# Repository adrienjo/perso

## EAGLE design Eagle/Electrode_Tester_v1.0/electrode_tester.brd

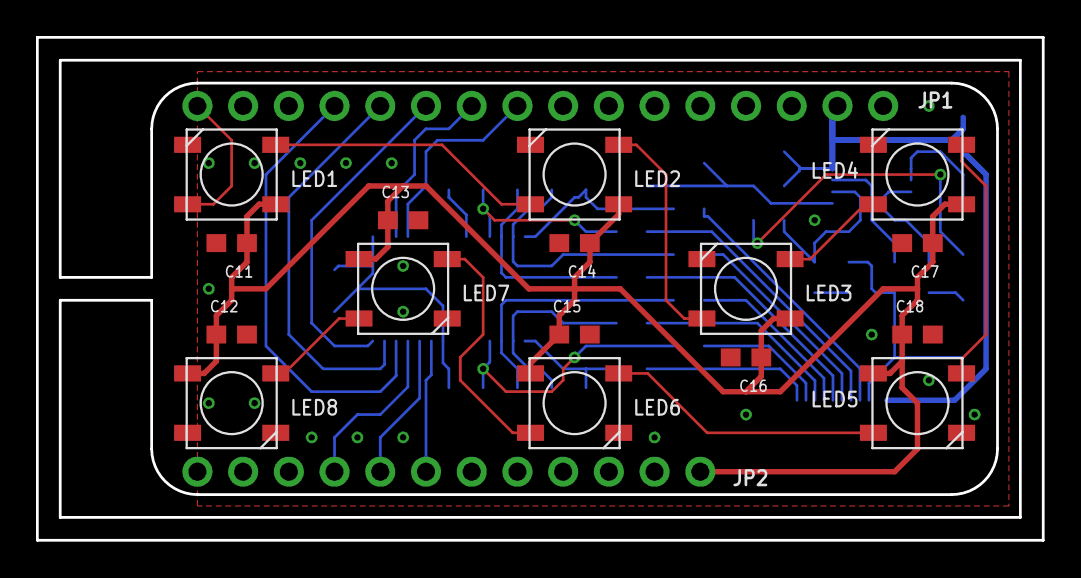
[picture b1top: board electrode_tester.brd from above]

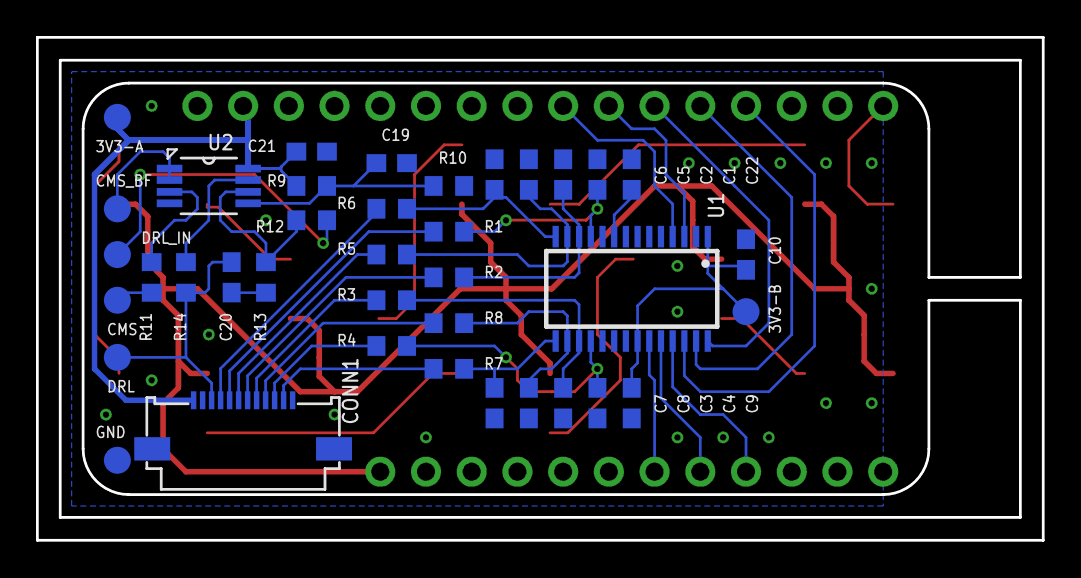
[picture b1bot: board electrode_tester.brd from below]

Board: 2 copper layers, 55.9 x 27.9 mm, 56 parts (38 on the bottom side), 45 nets.

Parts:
3V3-A, 3V3-B: TESTPAD_PROG; TP1.5MM
C1, C2, C3, C4, C5, C6, C7, C8, C9, C10, C11, C12, C13, C14, C15, C16, C17, C18, C19, C20, C21, C22: C0603
CMS: TESTPAD_PROG; TP1.5MM
CMS_BF: TESTPAD_PROG; TP1.5MM
CONN1: 505110-1292
DRL: TESTPAD_PROG; TP1.5MM
DRL_IN: TESTPAD_PROG; TP1.5MM
GND: TESTPAD_PROG; TP1.5MM
JP1: 1X16_ROUND
JP2: 1X12_ROUND
LED1, LED2, LED3, LED4, LED5, LED6, LED7, LED8: WS2812B5050; WS2812B
R1, R2, R3, R4, R5, R6, R7, R8, R9, R10, R11, R12, R13, R14: R0603
U1: ADS1248; TSSOP28
U2: LMP7702MM/NOPBVSSOP; VSSOP8

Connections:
3V3: 3V3-A.1, 3V3-B.1, C9.1, C10.1, C21.1, CONN1.12, JP1.15, R9.2, U1.1, U1.22, U2.8
ADC_/CS: JP2.8, U1.24
ADC_/DRDY: JP2.9, U1.25
ADC_/RST: JP1.8, U1.4
ADC_CLK: JP1.7, U1.3
ADC_START: JP2.7, U1.23
AIN0: C1.1, R1.2, U1.11
AIN1: C2.1, R2.2, U1.12
AIN2: C3.1, R3.2, U1.17
AIN3: C4.1, R4.2, U1.18
AIN4: C5.1, R5.2, U1.13
AIN5: C6.1, R6.2, U1.14
AIN6: C7.1, R7.2, U1.15
AIN7: C8.1, R8.2, U1.16
CMS: CMS.1, R11.2
CMS_BF: CMS_BF.1, U2.1, U2.2
DRL: C20.1, CONN1.10, DRL.1, R14.1
DRL_IN: DRL_IN.1, R12.1
E0: CONN1.8, R1.1
E1: CONN1.6, R2.1
E2: CONN1.5, R3.1
E3: CONN1.3, R4.1
E4: CONN1.7, R5.1
E5: CONN1.9, R6.1
E6: CONN1.2, R7.1
E7: CONN1.4, R8.1
GND: C1.2, C2.2, C3.2, C4.2, C5.2, C6.2, C7.2, C8.2, C9.2, C10.2, C11.2, C12.2, C13.2, C14.2, C15.2, C16.2, C17.2, C18.2, C19.2, C21.2, C22.2, CONN1.1, CONN1.MH1, CONN1.MH2, GND.1, JP1.13, LED1.3-GND, LED2.3-GND, LED3.3-GND, LED4.3-GND, LED5.3-GND, LED6.3-GND, LED7.3-GND, LED8.3-GND, R10.1, U1.2, U1.8, U1.10, U1.21, U2.4
LEDS_IN: JP1.1, LED1.4-DIN
unnamed: LED1.2-DOUT, LED2.4-DIN
unnamed: LED2.2-DOUT, LED3.4-DIN
unnamed: LED3.2-DOUT, LED4.4-DIN
unnamed: LED4.2-DOUT, LED5.4-DIN
unnamed: LED5.2-DOUT, LED6.4-DIN
unnamed: LED6.2-DOUT, LED7.4-DIN
unnamed: LED7.2-DOUT, LED8.4-DIN
unnamed: R11.1, U2.3
unnamed: C22.1, U1.9
unnamed: R12.2, R13.2, U2.6
unnamed: C20.2, R13.1
unnamed: R14.2, U2.7
unnamed: C19.1, R9.1, R10.2, U2.5
SPI_MISO: JP1.4, U1.26
SPI_MOSI: JP1.5, U1.27
SPI_SCLK: JP1.6, U1.28
VBAT: C11.1, C12.1, C13.1, C14.1, C15.1, C16.1, C17.1, C18.1, JP2.1, LED1.1-VDD, LED2.1-VDD, LED3.1-VDD, LED4.1-VDD, LED5.1-VDD, LED6.1-VDD, LED7.1-VDD, LED8.1-VDD

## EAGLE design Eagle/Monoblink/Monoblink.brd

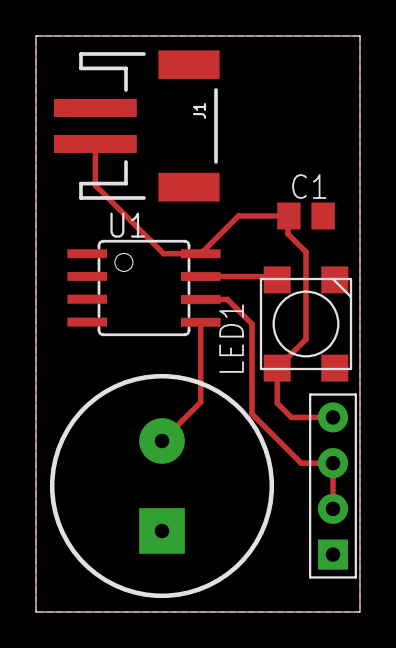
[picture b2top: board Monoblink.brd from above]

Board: 1 copper layer, 18.0 x 32.0 mm, 6 parts (0 on the bottom side), 5 nets.

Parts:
C1: C0805
J1: JST-2-SMD
LED1: NEOPIXEL; SMD5050
U1: ATTINY85; SOIC8
U$1: RF_CONN
U$2: PIEZO; PS1240P02BT

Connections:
GND: C1.2, J1.1, LED1.1, U1.4, U$1.1, U$2.V-
LED_DATA_IN: LED1.2, U1.7
PIEZO_IN: U1.5, U$2.V+
RF_DATA_OUT: U1.6, U$1.2, U$1.3
VCC: C1.1, J1.2, LED1.3, U1.8, U$1.4

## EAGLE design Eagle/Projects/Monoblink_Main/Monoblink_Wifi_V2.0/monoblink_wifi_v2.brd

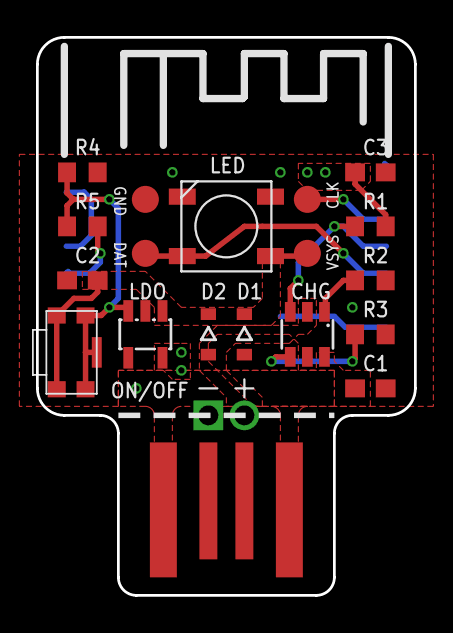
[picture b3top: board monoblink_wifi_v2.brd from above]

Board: 2 copper layers, 21.0 x 31.0 mm, 21 parts (1 on the bottom side), 13 nets.

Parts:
C1, C2: 0.1u; C0603
C3: C0603
CHG: BQ21040; SOT23-6
CLK: TESTPAD_PROG; TP1.5MM
D1, D2: NSR0320MW2T1G; SOD323
DAT: TESTPAD_PROG; TP1.5MM
GND: TESTPAD_PROG; TP1.5MM
LDO: TLV755P; SOT23-5
LED: WS2812B5050; WS2812B
LP402025: 150mAh; BATT_CON
ON/OFF: KMS231GPLFSNO_PEGS; KMS231GLFS
R1, R2, R5: 10K; R0603
R3: 6.8K; R0603
R4: 100K; R0603
U$2: USB_PCB; USB_PADS
VSYS: TESTPAD_PROG; TP1.5MM
WROOM-02: ESP-WROOM-02FRONT-FACE; FRONT-FACE

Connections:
/CHG: CHG.3, R1.2, WROOM-02.4
/SD: R5.1, WROOM-02.14
GND: C1.2, C2.2, C3.2, CHG.5, GND.1, LDO.2, LED.3-GND, LP402025.V-, R2.2, R3.2, R4.1, U$2.GND, WROOM-02.6, WROOM-02.9, WROOM-02.13, WROOM-02.18
IO16-RST: WROOM-02.15, WROOM-02.17
ISET: CHG.4, R3.1
LDO_EN: LDO.3, ON/OFF.2, ON/OFF.3, ON/OFF.4, R4.2, R5.2
LED_CLK: CLK.1, WROOM-02.3
LED_DATA: DAT.1, LED.4-DIN, WROOM-02.5
TS: CHG.1, R2.1
VBAT: CHG.2, D2.2, LP402025.V+
VCC_2V8: C3.1, LDO.5, R1.1, WROOM-02.1, WROOM-02.2, WROOM-02.7
VSYS: C2.1, D1.1, D2.1, LDO.1, LED.1-VDD, ON/OFF.1, ON/OFF.5, VSYS.1
VUSB_5V: C1.1, CHG.6, D1.2, U$2.V_SUPPLY

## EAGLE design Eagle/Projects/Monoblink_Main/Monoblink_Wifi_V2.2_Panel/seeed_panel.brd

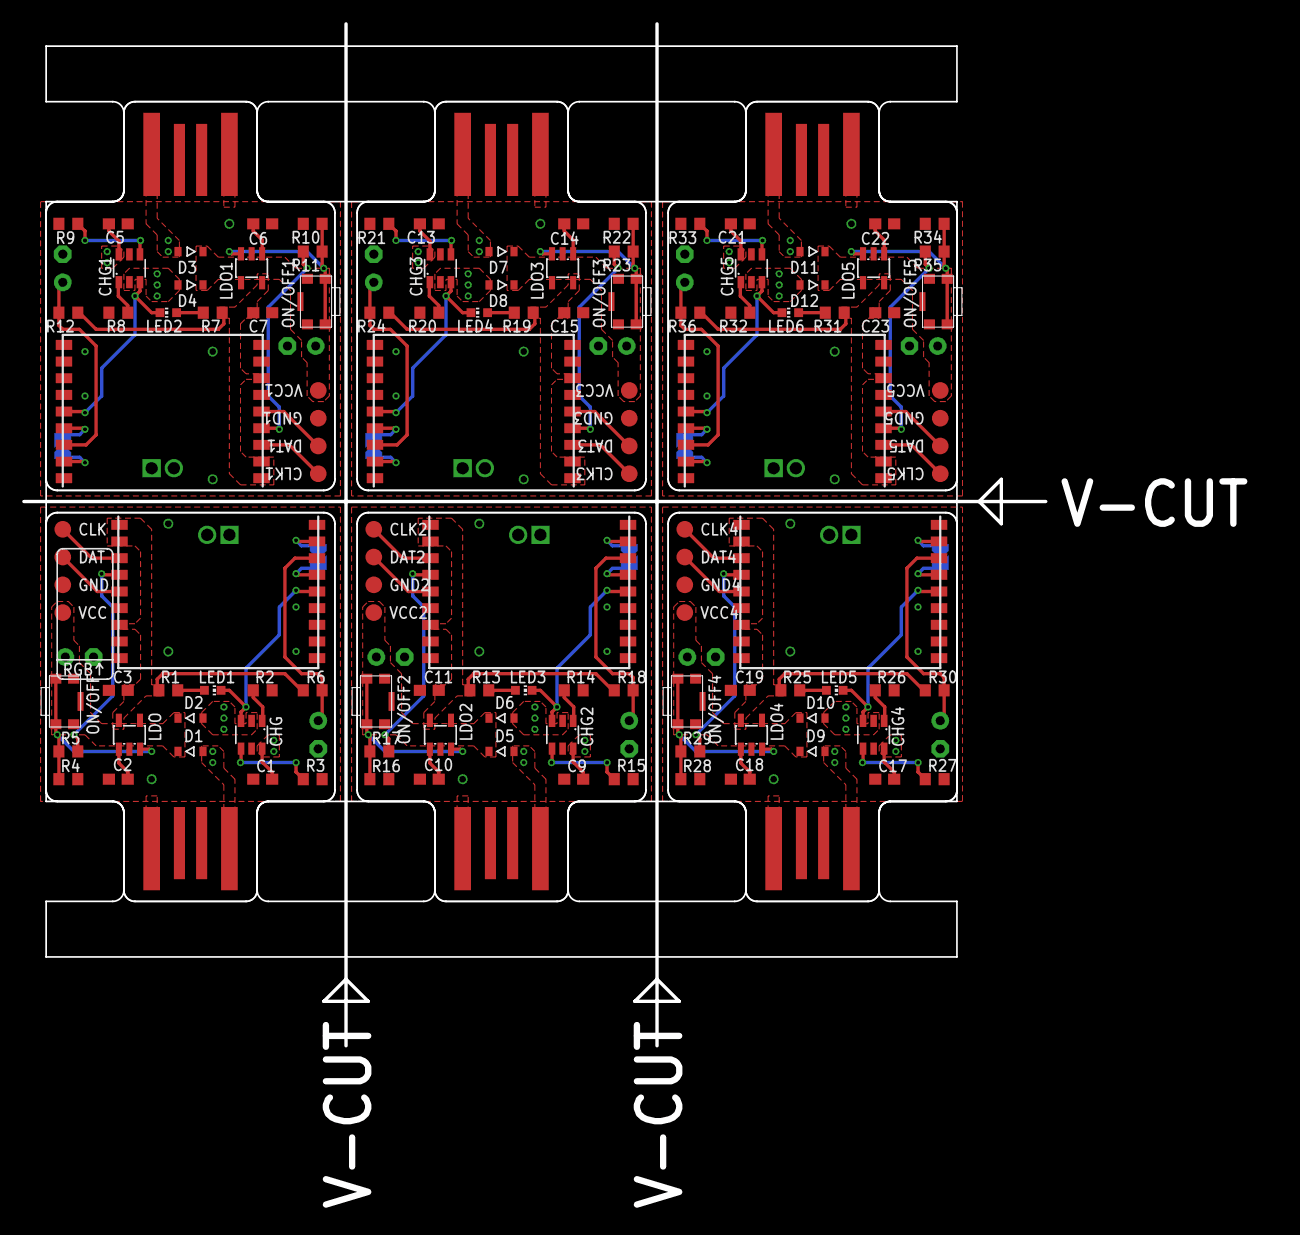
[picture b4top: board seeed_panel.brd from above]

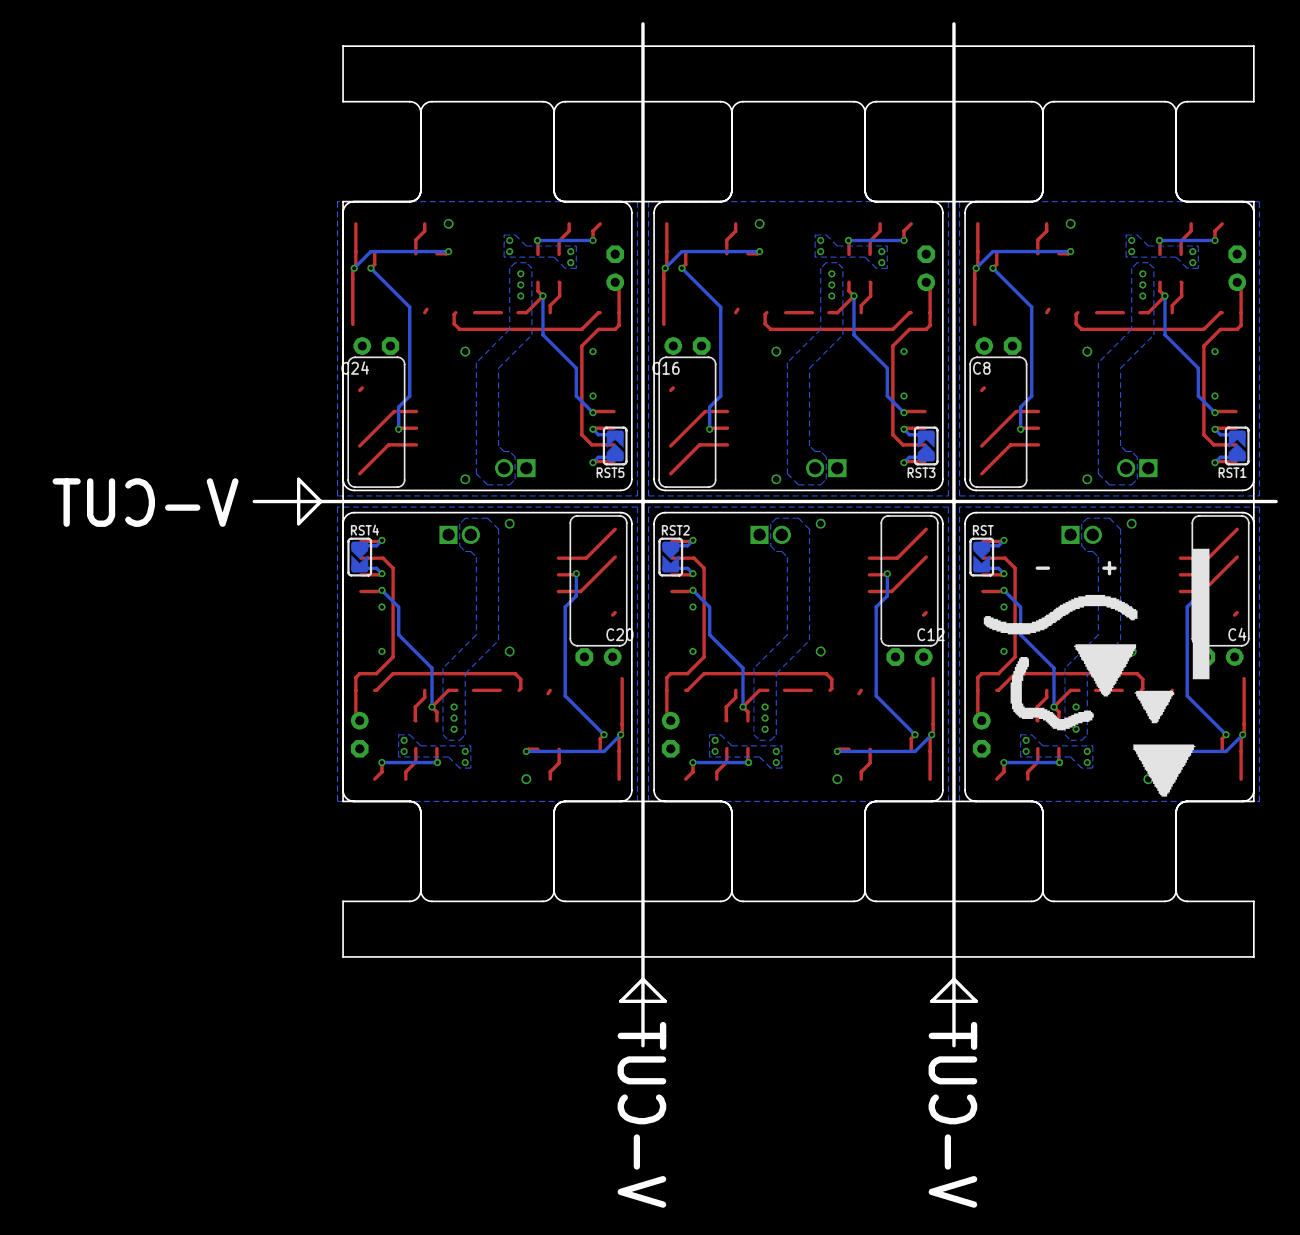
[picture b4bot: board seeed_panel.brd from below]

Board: 2 copper layers, 82.0 x 82.0 mm, 150 parts (12 on the bottom side), 96 nets.

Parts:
C1, C2, C5, C6, C9, C10, C13, C14, C17, C18, C21, C22: 0.1u; C0603
C3, C7, C11, C15, C19, C23: C0603
C4, C8, C12, C16, C20, C24: CAP_5MM_L; TT2D5L
CHG, CHG1, CHG2, CHG3, CHG4, CHG5: BQ21040; SOT23-6
CLK, CLK1, CLK2, CLK3, CLK4, CLK5: TESTPAD_PROG; TP1.5MM
D1, D2, D3, D4, D5, D6, D7, D8, D9, D10, D11, D12: NSR0320MW2T1G; SOD323
DAT, DAT1, DAT2, DAT3, DAT4, DAT5: TESTPAD_PROG; TP1.5MM
GND, GND1, GND2, GND3, GND4, GND5: TESTPAD_PROG; TP1.5MM
LDO, LDO1, LDO2, LDO3, LDO4, LDO5: TLV755P; SOT23-5
LED1, LED2, LED3, LED4, LED5, LED6: CHIP-LED0603
LP1, LP2, LP3, LP4, LP5, LP402025: 150mAh; BATT_CON
ON/OFF, ON/OFF1, ON/OFF2, ON/OFF3, ON/OFF4, ON/OFF5: KMS231GPLFSNO_PEGS; KMS231GLFS
R1, R7, R13, R19, R25, R31: 220; R0603
R2, R5, R6, R8, R11, R12, R14, R17, R18, R20, R23, R24, R26, R29, R30, R32, R35, R36: 10K; R0603
R3, R9, R15, R21, R27, R33: 6.8K; R0603
R4, R10, R16, R22, R28, R34: 100K; R0603
RST, RST1, RST2, RST3, RST4, RST5: SOLDERJUMPER_ARROW_NOPASTE
U$1, U$4, U$6, U$8, U$10, U$12: 2PIN_STD
U$2, U$3, U$5, U$7, U$9, U$11: USB_PCB; USB_PADS
VCC, VCC1, VCC2, VCC3, VCC4, VCC5: TESTPAD_PROG; TP1.5MM
WROOM-01, WROOM-02, WROOM-03, WROOM-04, WROOM-05, WROOM-06: ESP-WROOM-02FRONT-FACE; FRONT-FACE

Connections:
/CHG-/LED: CHG.3, LED1.C, WROOM-02.14
/CHG-/LED1: CHG1.3, LED2.C, WROOM-01.14
/CHG-/LED2: CHG2.3, LED3.C, WROOM-03.14
/CHG-/LED3: CHG3.3, LED4.C, WROOM-04.14
/CHG-/LED4: CHG4.3, LED5.C, WROOM-05.14
/CHG-/LED5: CHG5.3, LED6.C, WROOM-06.14
/SD: R5.1, WROOM-02.4
/SD1: R11.1, WROOM-01.4
/SD2: R17.1, WROOM-03.4
/SD3: R23.1, WROOM-04.4
/SD4: R29.1, WROOM-05.4
/SD5: R35.1, WROOM-06.4
A0: R6.1, U$1.+, WROOM-02.16
A1: R12.1, U$4.+, WROOM-01.16
A2: R18.1, U$6.+, WROOM-03.16
A3: R24.1, U$8.+, WROOM-04.16
A4: R30.1, U$10.+, WROOM-05.16
A5: R36.1, U$12.+, WROOM-06.16
GND: C1.2, C2.2, C3.2, C4.-, CHG.5, GND.1, LDO.2, LP402025.V-, R2.2, R3.2, R4.1, U$1.-, U$2.GND, WROOM-02.6, WROOM-02.9, WROOM-02.13, WROOM-02.18
GND1: C5.2, C6.2, C7.2, C8.-, CHG1.5, GND1.1, LDO1.2, LP1.V-, R8.2, R9.2, R10.1, U$3.GND, U$4.-, WROOM-01.6, WROOM-01.9, WROOM-01.13, WROOM-01.18
GND2: C9.2, C10.2, C11.2, C12.-, CHG2.5, GND2.1, LDO2.2, LP2.V-, R14.2, R15.2, R16.1, U$5.GND, U$6.-, WROOM-03.6, WROOM-03.9, WROOM-03.13, WROOM-03.18
GND3: C13.2, C14.2, C15.2, C16.-, CHG3.5, GND3.1, LDO3.2, LP3.V-, R20.2, R21.2, R22.1, U$7.GND, U$8.-, WROOM-04.6, WROOM-04.9, WROOM-04.13, WROOM-04.18
GND4: C17.2, C18.2, C19.2, C20.-, CHG4.5, GND4.1, LDO4.2, LP4.V-, R26.2, R27.2, R28.1, U$9.GND, U$10.-, WROOM-05.6, WROOM-05.9, WROOM-05.13, WROOM-05.18
GND5: C21.2, C22.2, C23.2, C24.-, CHG5.5, GND5.1, LDO5.2, LP5.V-, R32.2, R33.2, R34.1, U$11.GND, U$12.-, WROOM-06.6, WROOM-06.9, WROOM-06.13, WROOM-06.18
IO3: RST1.1, WROOM-01.17
IO7: RST2.1, WROOM-03.17
IO10: RST3.1, WROOM-04.17
IO13: RST4.1, WROOM-05.17
IO16: RST.1, WROOM-02.17
IO17: RST5.1, WROOM-06.17
ISET: CHG.4, R3.1
ISET1: CHG1.4, R9.1
ISET2: CHG2.4, R15.1
ISET3: CHG3.4, R21.1
ISET4: CHG4.4, R27.1
ISET5: CHG5.4, R33.1
LDO_EN: LDO.3, ON/OFF.1, ON/OFF.5, R4.2, R5.2
LDO_EN1: LDO1.3, ON/OFF1.1, ON/OFF1.5, R10.2, R11.2
LDO_EN2: LDO2.3, ON/OFF2.1, ON/OFF2.5, R16.2, R17.2
LDO_EN3: LDO3.3, ON/OFF3.1, ON/OFF3.5, R22.2, R23.2
LDO_EN4: LDO4.3, ON/OFF4.1, ON/OFF4.5, R28.2, R29.2
LDO_EN5: LDO5.3, ON/OFF5.1, ON/OFF5.5, R34.2, R35.2
LED_CLK: CLK.1, WROOM-02.3
LED_CLK1: CLK1.1, WROOM-01.3
LED_CLK2: CLK2.1, WROOM-03.3
LED_CLK3: CLK3.1, WROOM-04.3
LED_CLK4: CLK4.1, WROOM-05.3
LED_CLK5: CLK5.1, WROOM-06.3
LED_DATA: DAT.1, WROOM-02.5
LED_DATA1: DAT1.1, WROOM-01.5
LED_DATA2: DAT2.1, WROOM-03.5
LED_DATA3: DAT3.1, WROOM-04.5
LED_DATA4: DAT4.1, WROOM-05.5
LED_DATA5: DAT5.1, WROOM-06.5
unnamed: LED1.A, R1.2
unnamed: LED2.A, R7.2
unnamed: LED3.A, R13.2
unnamed: LED4.A, R19.2
unnamed: LED5.A, R25.2
unnamed: LED6.A, R31.2
RST: RST.2, WROOM-02.15
RST1: RST1.2, WROOM-01.15
RST2: RST2.2, WROOM-03.15
RST3: RST3.2, WROOM-04.15
RST4: RST4.2, WROOM-05.15
RST5: RST5.2, WROOM-06.15
TS: CHG.1, R2.1
TS1: CHG1.1, R8.1
TS2: CHG2.1, R14.1
TS3: CHG3.1, R20.1
TS4: CHG4.1, R26.1
TS5: CHG5.1, R32.1
VBAT: CHG.2, D2.2, LP402025.V+
VBAT1: CHG1.2, D4.2, LP1.V+
VBAT2: CHG2.2, D6.2, LP2.V+
VBAT3: CHG3.2, D8.2, LP3.V+
VBAT4: CHG4.2, D10.2, LP4.V+
VBAT5: CHG5.2, D12.2, LP5.V+
VCC: C2.1, C4.+, D1.1, D2.1, LDO.1, ON/OFF.2, ON/OFF.3, ON/OFF.4, VCC.1
VCC1: C6.1, C8.+, D3.1, D4.1, LDO1.1, ON/OFF1.2, ON/OFF1.3, ON/OFF1.4, VCC1.1
VCC2: C10.1, C12.+, D5.1, D6.1, LDO2.1, ON/OFF2.2, ON/OFF2.3, ON/OFF2.4, VCC2.1
VCC3: C14.1, C16.+, D7.1, D8.1, LDO3.1, ON/OFF3.2, ON/OFF3.3, ON/OFF3.4, VCC3.1
VCC4: C18.1, C20.+, D9.1, D10.1, LDO4.1, ON/OFF4.2, ON/OFF4.3, ON/OFF4.4, VCC4.1
VCC5: C22.1, C24.+, D11.1, D12.1, LDO5.1, ON/OFF5.2, ON/OFF5.3, ON/OFF5.4, VCC5.1
VDD: C3.1, LDO.5, R1.1, R6.2, WROOM-02.1, WROOM-02.2, WROOM-02.7
VDD1: C7.1, LDO1.5, R7.1, R12.2, WROOM-01.1, WROOM-01.2, WROOM-01.7
VDD2: C11.1, LDO2.5, R13.1, R18.2, WROOM-03.1, WROOM-03.2, WROOM-03.7
VDD3: C15.1, LDO3.5, R19.1, R24.2, WROOM-04.1, WROOM-04.2, WROOM-04.7
VDD4: C19.1, LDO4.5, R25.1, R30.2, WROOM-05.1, WROOM-05.2, WROOM-05.7
VDD5: C23.1, LDO5.5, R31.1, R36.2, WROOM-06.1, WROOM-06.2, WROOM-06.7
VUSB_5V: C1.1, CHG.6, D1.2, U$2.V_SUPPLY
VUSB_5V1: C5.1, CHG1.6, D3.2, U$3.V_SUPPLY
VUSB_5V2: C9.1, CHG2.6, D5.2, U$5.V_SUPPLY
VUSB_5V3: C13.1, CHG3.6, D7.2, U$7.V_SUPPLY
VUSB_5V4: C17.1, CHG4.6, D9.2, U$9.V_SUPPLY
VUSB_5V5: C21.1, CHG5.6, D11.2, U$11.V_SUPPLY

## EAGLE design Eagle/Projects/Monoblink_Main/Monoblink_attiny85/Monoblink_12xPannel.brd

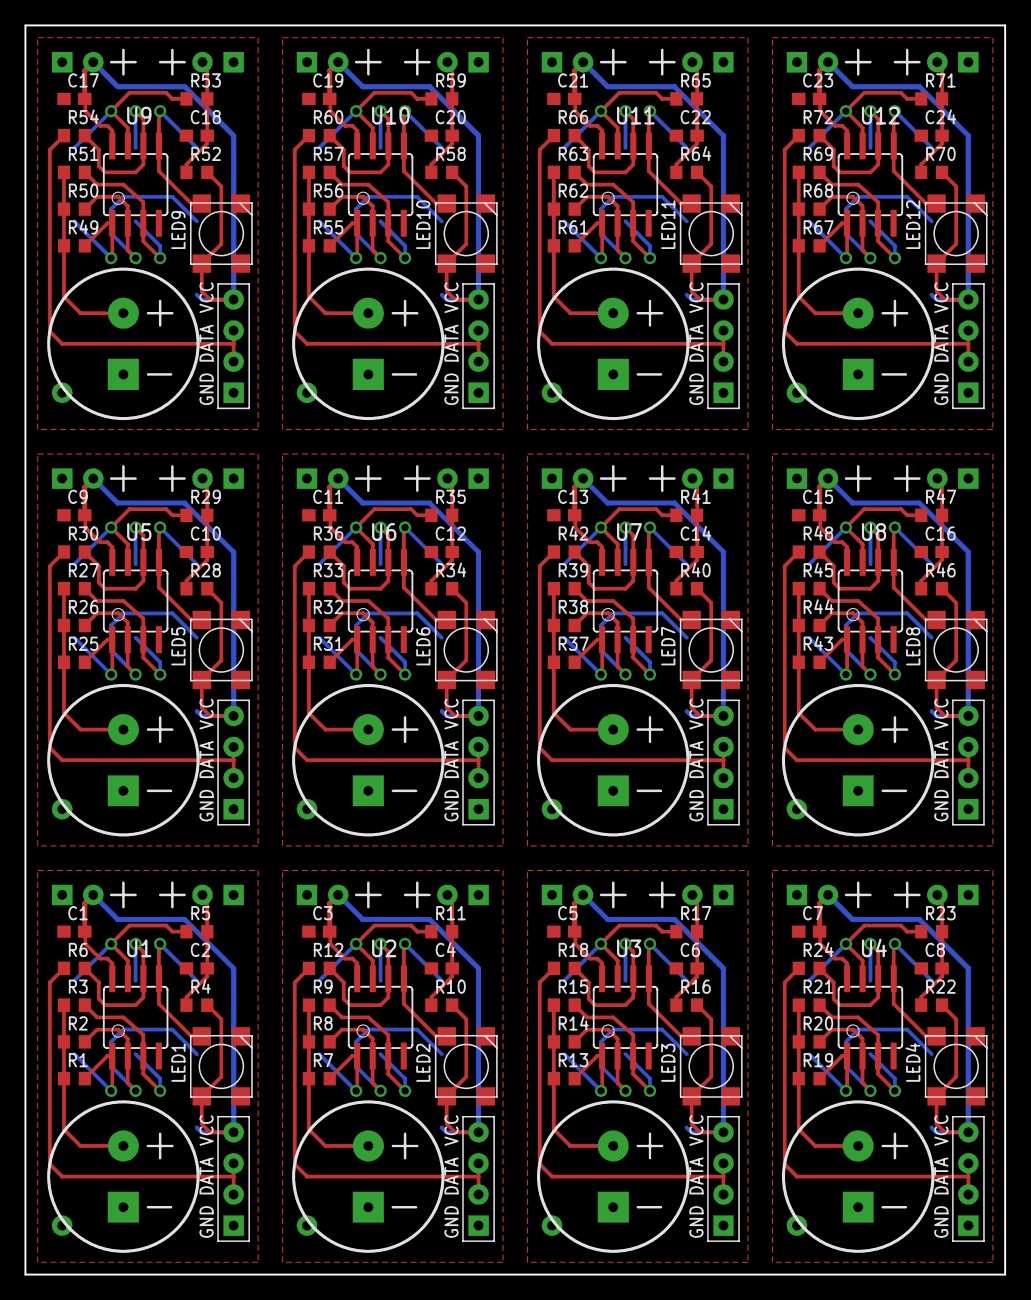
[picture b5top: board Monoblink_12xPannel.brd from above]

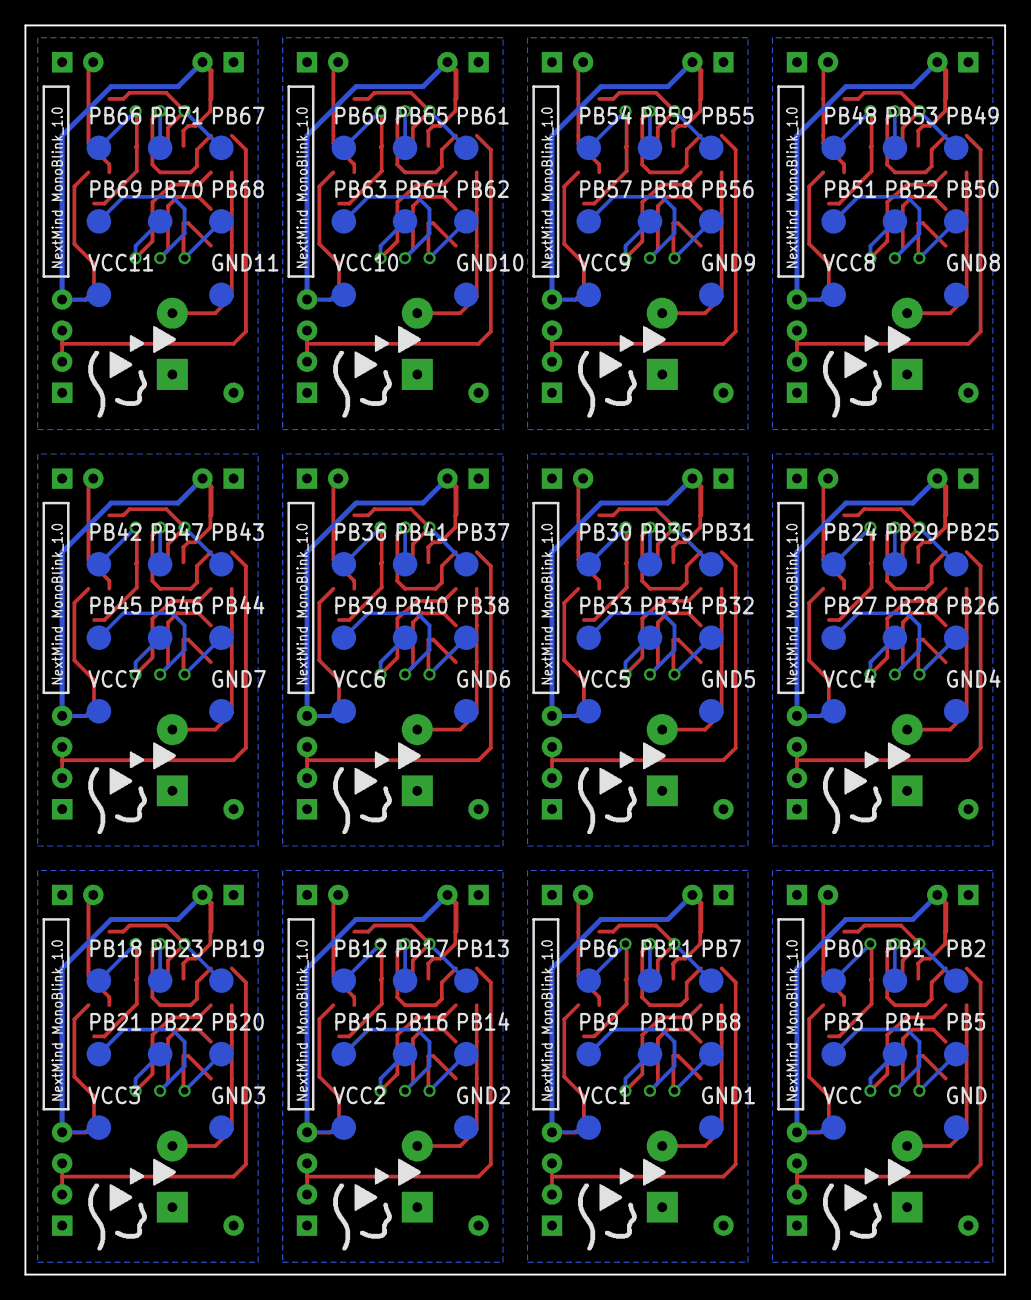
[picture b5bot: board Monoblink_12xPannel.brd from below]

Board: 2 copper layers, 80.0 x 102.0 mm, 264 parts (96 on the bottom side), 132 nets.

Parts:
C1, C2, C3, C4, C5, C6, C7, C8, C9, C10, C11, C12, C13, C14, C15, C16, C17, C18, C19, C20, C21, C22, C23, C24: 100n; C0603
GND, GND1, GND2, GND3, GND4, GND5, GND6, GND7, GND8, GND9, GND10, GND11: TESTPAD_PROG_BOARD; TP2MM
LED1, LED2, LED3, LED4, LED5, LED6, LED7, LED8, LED9, LED10, LED11, LED12: NEOPIXEL; SMD5050
PB0, PB1, PB2, PB3, PB4, PB5, PB6, PB7, PB8, PB9, PB10, PB11, PB12, PB13, PB14, PB15, PB16, PB17, PB18, PB19, PB20, PB21, PB22, PB23, PB24, PB25, PB26, PB27, PB28, PB29, PB30, PB31, PB32, PB33, PB34, PB35, PB36, PB37, PB38, PB39, PB40, PB41, PB42, PB43, PB44, PB45, PB46, PB47, PB48, PB49, PB50, PB51, PB52, PB53, PB54, PB55, PB56, PB57, PB58, PB59, PB60, PB61, PB62, PB63, PB64, PB65, PB66, PB67, PB68, PB69, PB70, PB71: TESTPAD_PROG_BOARD; TP2MM
R1, R7, R13, R19, R25, R31, R37, R43, R49, R55, R61, R67: 50; R0603
R2, R8, R14, R20, R26, R32, R38, R44, R50, R56, R62, R68: 200; R0603
R3, R9, R15, R21, R27, R33, R39, R45, R51, R57, R63, R69: 100; R0603
R4, R10, R16, R22, R28, R34, R40, R46, R52, R58, R64, R70: 10K; R0603
R5, R6, R11, R12, R17, R18, R23, R24, R29, R30, R35, R36, R41, R42, R47, R48, R53, R54, R59, R60, R65, R66, R71, R72: 100K; R0603
U1, U2, U3, U4, U5, U6, U7, U8, U9, U10, U11, U12: ATTINY85; SOIC8
U$1, U$5, U$9, U$13, U$17, U$21, U$25, U$29, U$33, U$37, U$41, U$45: RF_CONN
U$2, U$6, U$10, U$14, U$18, U$22, U$26, U$30, U$34, U$38, U$42, U$46: PIEZO; PS1240P02BT
U$3, U$7, U$11, U$15, U$19, U$23, U$27, U$31, U$35, U$39, U$43, U$47: BATT_TH; TWO_TH
U$4, U$8, U$12, U$16, U$20, U$24, U$28, U$32, U$36, U$40, U$44, U$48: SNSR_CONN; TWO_TH
VCC, VCC1, VCC2, VCC3, VCC4, VCC5, VCC6, VCC7, VCC8, VCC9, VCC10, VCC11: TESTPAD_PROG_BOARD; TP2MM

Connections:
GND: C1.2, C2.2, GND.1, LED1.1, U1.4, U$1.1, U$2.V-, U$3.GND, U$4.GND
GND1: C3.2, C4.2, GND1.1, LED2.1, U2.4, U$5.1, U$6.V-, U$7.GND, U$8.GND
GND2: C5.2, C6.2, GND2.1, LED3.1, U3.4, U$9.1, U$10.V-, U$11.GND, U$12.GND
GND3: C7.2, C8.2, GND3.1, LED4.1, U4.4, U$13.1, U$14.V-, U$15.GND, U$16.GND
GND4: C9.2, C10.2, GND4.1, LED5.1, U5.4, U$17.1, U$18.V-, U$19.GND, U$20.GND
GND5: C11.2, C12.2, GND5.1, LED6.1, U6.4, U$21.1, U$22.V-, U$23.GND, U$24.GND
GND6: C13.2, C14.2, GND6.1, LED7.1, U7.4, U$25.1, U$26.V-, U$27.GND, U$28.GND
GND7: C15.2, C16.2, GND7.1, LED8.1, U8.4, U$29.1, U$30.V-, U$31.GND, U$32.GND
GND8: C17.2, C18.2, GND8.1, LED9.1, U9.4, U$33.1, U$34.V-, U$35.GND, U$36.GND
GND9: C19.2, C20.2, GND9.1, LED10.1, U10.4, U$37.1, U$38.V-, U$39.GND, U$40.GND
GND10: C21.2, C22.2, GND10.1, LED11.1, U11.4, U$41.1, U$42.V-, U$43.GND, U$44.GND
GND11: C23.2, C24.2, GND11.1, LED12.1, U12.4, U$45.1, U$46.V-, U$47.GND, U$48.GND
PB0: LED1.2, PB0.1, U1.5
PB1: PB1.1, R6.1, U1.6
PB2: PB2.1, R5.2, U1.7
PB3: PB3.1, R2.1, U1.2
PB4: PB4.1, R3.1, U1.3
PB5: PB5.1, R1.1, U1.1
PB6: PB8.1, R7.1, U2.1
PB7: PB10.1, R9.1, U2.3
PB8: PB9.1, R8.1, U2.2
PB9: PB7.1, R11.2, U2.7
PB10: PB11.1, R12.1, U2.6
PB11: LED2.2, PB6.1, U2.5
PB12: PB14.1, R13.1, U3.1
PB13: PB16.1, R15.1, U3.3
PB14: PB15.1, R14.1, U3.2
PB15: PB13.1, R17.2, U3.7
PB16: PB17.1, R18.1, U3.6
PB17: LED3.2, PB12.1, U3.5
PB18: PB20.1, R19.1, U4.1
PB19: PB22.1, R21.1, U4.3
PB20: PB21.1, R20.1, U4.2
PB21: PB19.1, R23.2, U4.7
PB22: PB23.1, R24.1, U4.6
PB23: LED4.2, PB18.1, U4.5
PB24: PB26.1, R25.1, U5.1
PB25: PB28.1, R27.1, U5.3
PB26: PB27.1, R26.1, U5.2
PB27: PB25.1, R29.2, U5.7
PB28: PB29.1, R30.1, U5.6
PB29: LED5.2, PB24.1, U5.5
PB30: PB32.1, R31.1, U6.1
PB31: PB34.1, R33.1, U6.3
PB32: PB33.1, R32.1, U6.2
PB33: PB31.1, R35.2, U6.7
PB34: PB35.1, R36.1, U6.6
PB35: LED6.2, PB30.1, U6.5
PB36: PB38.1, R37.1, U7.1
PB37: PB40.1, R39.1, U7.3
PB38: PB39.1, R38.1, U7.2
PB39: PB37.1, R41.2, U7.7
PB40: PB41.1, R42.1, U7.6
PB41: LED7.2, PB36.1, U7.5
PB42: PB44.1, R43.1, U8.1
PB43: PB46.1, R45.1, U8.3
PB44: PB45.1, R44.1, U8.2
PB45: PB43.1, R47.2, U8.7
PB46: PB47.1, R48.1, U8.6
PB47: LED8.2, PB42.1, U8.5
PB48: PB50.1, R49.1, U9.1
PB49: PB52.1, R51.1, U9.3
PB50: PB51.1, R50.1, U9.2
PB51: PB49.1, R53.2, U9.7
PB52: PB53.1, R54.1, U9.6
PB53: LED9.2, PB48.1, U9.5
PB54: PB56.1, R55.1, U10.1
PB55: PB58.1, R57.1, U10.3
PB56: PB57.1, R56.1, U10.2
PB57: PB55.1, R59.2, U10.7
PB58: PB59.1, R60.1, U10.6
PB59: LED10.2, PB54.1, U10.5
PB60: PB62.1, R61.1, U11.1
PB61: PB64.1, R63.1, U11.3
PB62: PB63.1, R62.1, U11.2
PB63: PB61.1, R65.2, U11.7
PB64: PB65.1, R66.1, U11.6
PB65: LED11.2, PB60.1, U11.5
PB66: PB68.1, R67.1, U12.1
PB67: PB70.1, R69.1, U12.3
PB68: PB69.1, R68.1, U12.2
PB69: PB67.1, R71.2, U12.7
PB70: PB71.1, R72.1, U12.6
PB71: LED12.2, PB66.1, U12.5
PIEZO_IN: R1.2, R2.2, R3.2, U$2.V+
PIEZO_IN1: R7.2, R8.2, R9.2, U$6.V+
PIEZO_IN2: R13.2, R14.2, R15.2, U$10.V+
PIEZO_IN3: R19.2, R20.2, R21.2, U$14.V+
PIEZO_IN4: R25.2, R26.2, R27.2, U$18.V+
PIEZO_IN5: R31.2, R32.2, R33.2, U$22.V+
PIEZO_IN6: R37.2, R38.2, R39.2, U$26.V+
PIEZO_IN7: R43.2, R44.2, R45.2, U$30.V+
PIEZO_IN8: R49.2, R50.2, R51.2, U$34.V+
PIEZO_IN9: R55.2, R56.2, R57.2, U$38.V+
PIEZO_IN10: R61.2, R62.2, R63.2, U$42.V+
PIEZO_IN11: R67.2, R68.2, R69.2, U$46.V+
RF_DATA_OUT: R6.2, U$1.2, U$1.3
RF_DATA_OUT1: R12.2, U$5.2, U$5.3
RF_DATA_OUT2: R18.2, U$9.2, U$9.3
RF_DATA_OUT3: R24.2, U$13.2, U$13.3
RF_DATA_OUT4: R30.2, U$17.2, U$17.3
RF_DATA_OUT5: R36.2, U$21.2, U$21.3
RF_DATA_OUT6: R42.2, U$25.2, U$25.3
RF_DATA_OUT7: R48.2, U$29.2, U$29.3
RF_DATA_OUT8: R54.2, U$33.2, U$33.3
RF_DATA_OUT9: R60.2, U$37.2, U$37.3
RF_DATA_OUT10: R66.2, U$41.2, U$41.3
RF_DATA_OUT11: R72.2, U$45.2, U$45.3
SENSOR_OUT: C2.1, R4.1, R5.1, U$4.VBAT
SENSOR_OUT1: C4.1, R10.1, R11.1, U$8.VBAT
SENSOR_OUT2: C6.1, R16.1, R17.1, U$12.VBAT
SENSOR_OUT3: C8.1, R22.1, R23.1, U$16.VBAT
SENSOR_OUT4: C10.1, R28.1, R29.1, U$20.VBAT
SENSOR_OUT5: C12.1, R34.1, R35.1, U$24.VBAT
SENSOR_OUT6: C14.1, R40.1, R41.1, U$28.VBAT
SENSOR_OUT7: C16.1, R46.1, R47.1, U$32.VBAT
SENSOR_OUT8: C18.1, R52.1, R53.1, U$36.VBAT
SENSOR_OUT9: C20.1, R58.1, R59.1, U$40.VBAT
SENSOR_OUT10: C22.1, R64.1, R65.1, U$44.VBAT
SENSOR_OUT11: C24.1, R70.1, R71.1, U$48.VBAT
VCC: C1.1, LED1.3, R4.2, U1.8, U$1.4, U$3.VBAT, VCC.1
VCC1: C3.1, LED2.3, R10.2, U2.8, U$5.4, U$7.VBAT, VCC1.1
VCC2: C5.1, LED3.3, R16.2, U3.8, U$9.4, U$11.VBAT, VCC2.1
VCC3: C7.1, LED4.3, R22.2, U4.8, U$13.4, U$15.VBAT, VCC3.1
VCC4: C9.1, LED5.3, R28.2, U5.8, U$17.4, U$19.VBAT, VCC4.1
VCC5: C11.1, LED6.3, R34.2, U6.8, U$21.4, U$23.VBAT, VCC5.1
VCC6: C13.1, LED7.3, R40.2, U7.8, U$25.4, U$27.VBAT, VCC6.1
VCC7: C15.1, LED8.3, R46.2, U8.8, U$29.4, U$31.VBAT, VCC7.1
VCC8: C17.1, LED9.3, R52.2, U9.8, U$33.4, U$35.VBAT, VCC8.1
VCC9: C19.1, LED10.3, R58.2, U10.8, U$37.4, U$39.VBAT, VCC9.1
VCC10: C21.1, LED11.3, R64.2, U11.8, U$41.4, U$43.VBAT, VCC10.1
VCC11: C23.1, LED12.3, R70.2, U12.8, U$45.4, U$47.VBAT, VCC11.1
